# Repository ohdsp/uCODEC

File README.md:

# [Open Hardware DSP Platform](www.ohdsp.org)
## uCODEC 1.0 
### A 5cm x 5cm CODEC board using Analog Device AD1939
### 8 Differential Outputs
### 4 Differential Inputs
---
# README
### Disclaimer
Copyright Paul Janicki 2019

Licensed under the TAPR Open Hardware License (www.tapr.org/OHL)

This documentation is distributed WITHOUT ANY EXPRESS OR IMPLIED WARRANTY, INCLUDING OF MERCHANTABILITY, SATISFACTORY QUALITY AND FITNESS FOR A PARTICULAR PURPOSE.

### What is this repository for?

**Quick summary**

This is a simple 4 input, 8 output, ADC/DAC board using the Analog Devices AD1939 CODEC

This board forms part the of the open hardware DSP platform which is designed to be a highly customisable and flexible DSP platform. 

This repository contains the KiCad design files, manufacturing Gerber/drill files, and PDF/drawing files for this board.

### What is the project folder structure?
Most folder names are self explanatory. Starting from the top level:
*uCODEC*
+ *Bill of Materials*  - This contains the bill of materials in CVS, LibreOffice Calc and XML formats
+ *Drawings* - This contains PDF and SVG Schematic and PCB files
+ *Gerbers* - This contains the PCB Gerbers and drill drawings for manufacture, there is also a zip file ready to send to most manufacturers
+ *KiCad* - This contains the original KiCad schematic and PCB design files

### How do I get set up?

**Summary of set up**

1. Set your self up a directory on a local disk, something simple will make life easier (eg C:\Electronics on Windows as used here), but anywhere will do just fine.
2. Download the Kicad-Libs from [https://github.com/ohdsp/KiCad-Libs](https://github.com/ohdsp/KiCad-Libs) and place in C:\Electronics\Kicad-Libs (or your chosen folder) 
3. Create a OHDSP subdirectory in C:\Electronics (so C:\Electronics\OHDSP)
3. Download this project to C:\Electronics\OHDSP\uCODEC
4. Fire up Kicad
5. Open the main project file C:\Electronics\OHDSP\uCODEC\KiCad\uCODEC.pro
7. Do as you wish with the project, just keep it under the TAPR Open Hardware License.
Note: For library issues see below.

Make sure your git setup doesn't exclude files used in the project (like .LIB files) or things may go wrong down the line.

**KiCad Library Configuration**

Note that libraries are setup using relative paths, if you follow the above instructions things should work just fine. Below is the default library setup.

To setup eeschema component libraries:
From KiCad main window go to menu Tools -> Edit Schematic Symbols. In the new Window go to menu Preferences -> Manage Symbol Libraries.

On the new "Symbol Libraries" window select the "Project Specific Libraries" tab. The "Append Library" and "Remove Library" buttons can be used to add/remove enteries.
The standard setup is:

|   | Active | Nickname        | Library Path                                        | Plugin Type | Options | Description |
|---|--------|-----------------|-----------------------------------------------------|-------------|---------|-------------|
| 1 | Ticked | power           | ${KICAD_SYMBOL_DIR}/power.lib                       | Legacy      | (blank) | (blank)     |
| 2 | Ticked | MyKiCadLibs-Lib | ${KIPRJMOD}/../../../KiCad-Libs/MyKiCadLibs-Lib.lib | Legacy      | (blank) | (blank)     |

${KICAD_SYMBOL_DIR}  is set under the Enviromnet Variable Configuration. Close Symbol Libraries dialogue and go "Preferences" -> "Configure Paths..."

${KICAD_SYMBOL_DIR} is set to C:\Program Files\KiCad\share\kicad\library - this is the default for a KiCad install on the C drive

${KIPRJMOD} is automatically set to the location of the project (.pro file), in this example this would be C:\Electronics\OHDSP\uCODEC\KiCad

To setup Pcbnew libraries:
From KiCad main window go to menu Tools -> Edit PCB Footprints. In the new Window go to menu Preferences -> Manage Symbol Libraries.

On the new "Symbol Libraries" window select the "Project Specific Libraries" tab. The "Append Library" and "Remove Library" buttons can be used to add/remove enteries.
The standard setup is:

|   | Active | Nickname               | Library Path                                                  | Plugin Type | Options | Description |
|---|--------|------------------------|---------------------------------------------------------------|-------------|---------|-------------|
| 1 | Ticked | MyKiCadLibs-Footprints | ${KIPRJMOD}/../../../KiCad-Libs/MyKiCadLibs-Footprints.pretty | KiCad       | (blank) | (blank)     |

${KIPRJMOD} is automatically set to the location of the project (.pro file), in this example this would be C:\Electronics\OHDSP\uCODEC\KiCad

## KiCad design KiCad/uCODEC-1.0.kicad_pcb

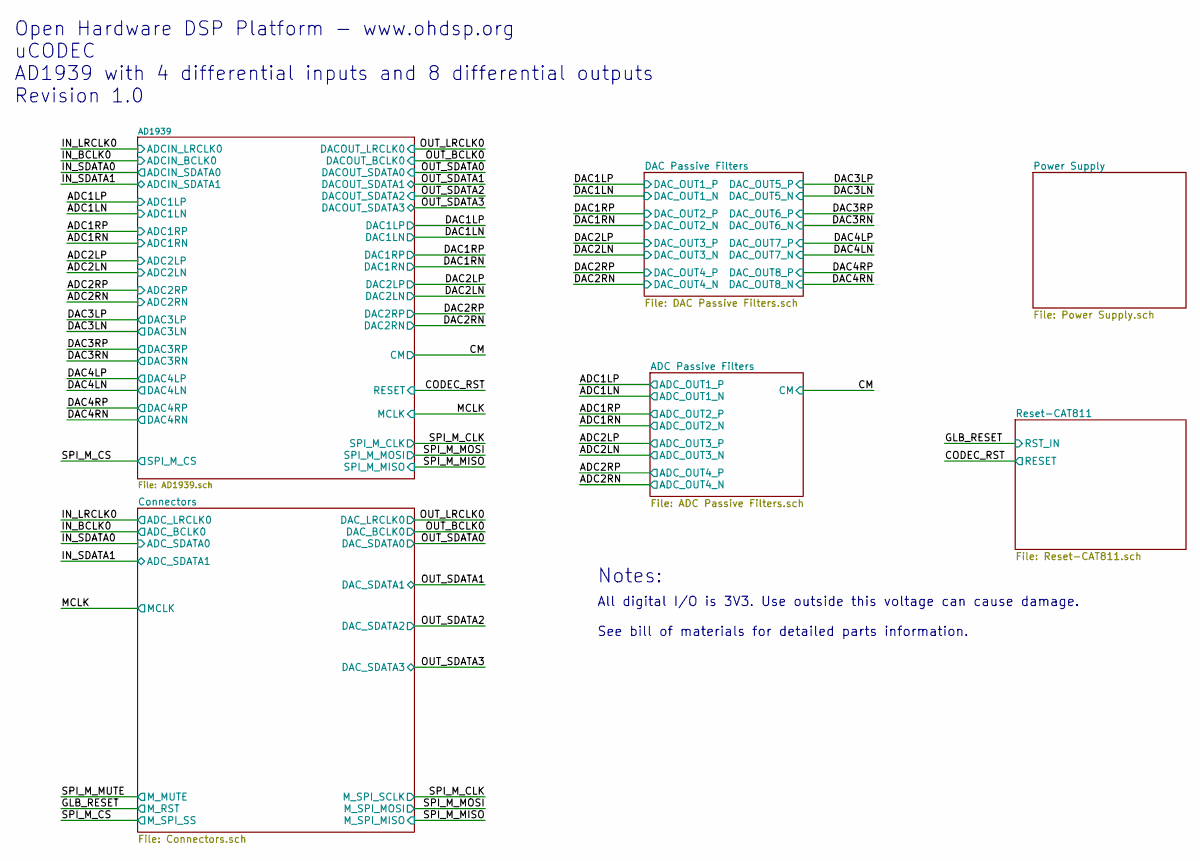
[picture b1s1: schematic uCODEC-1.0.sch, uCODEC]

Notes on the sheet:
All digital I/O is 3V3. Use outside this voltage can cause damage. See bill of materials for detailed parts information.
Notes:
Open Hardware DSP Platform - www.ohdsp.org uCODEC AD1939 with 4 differential inputs and 8 differential outputs Revision 1.0

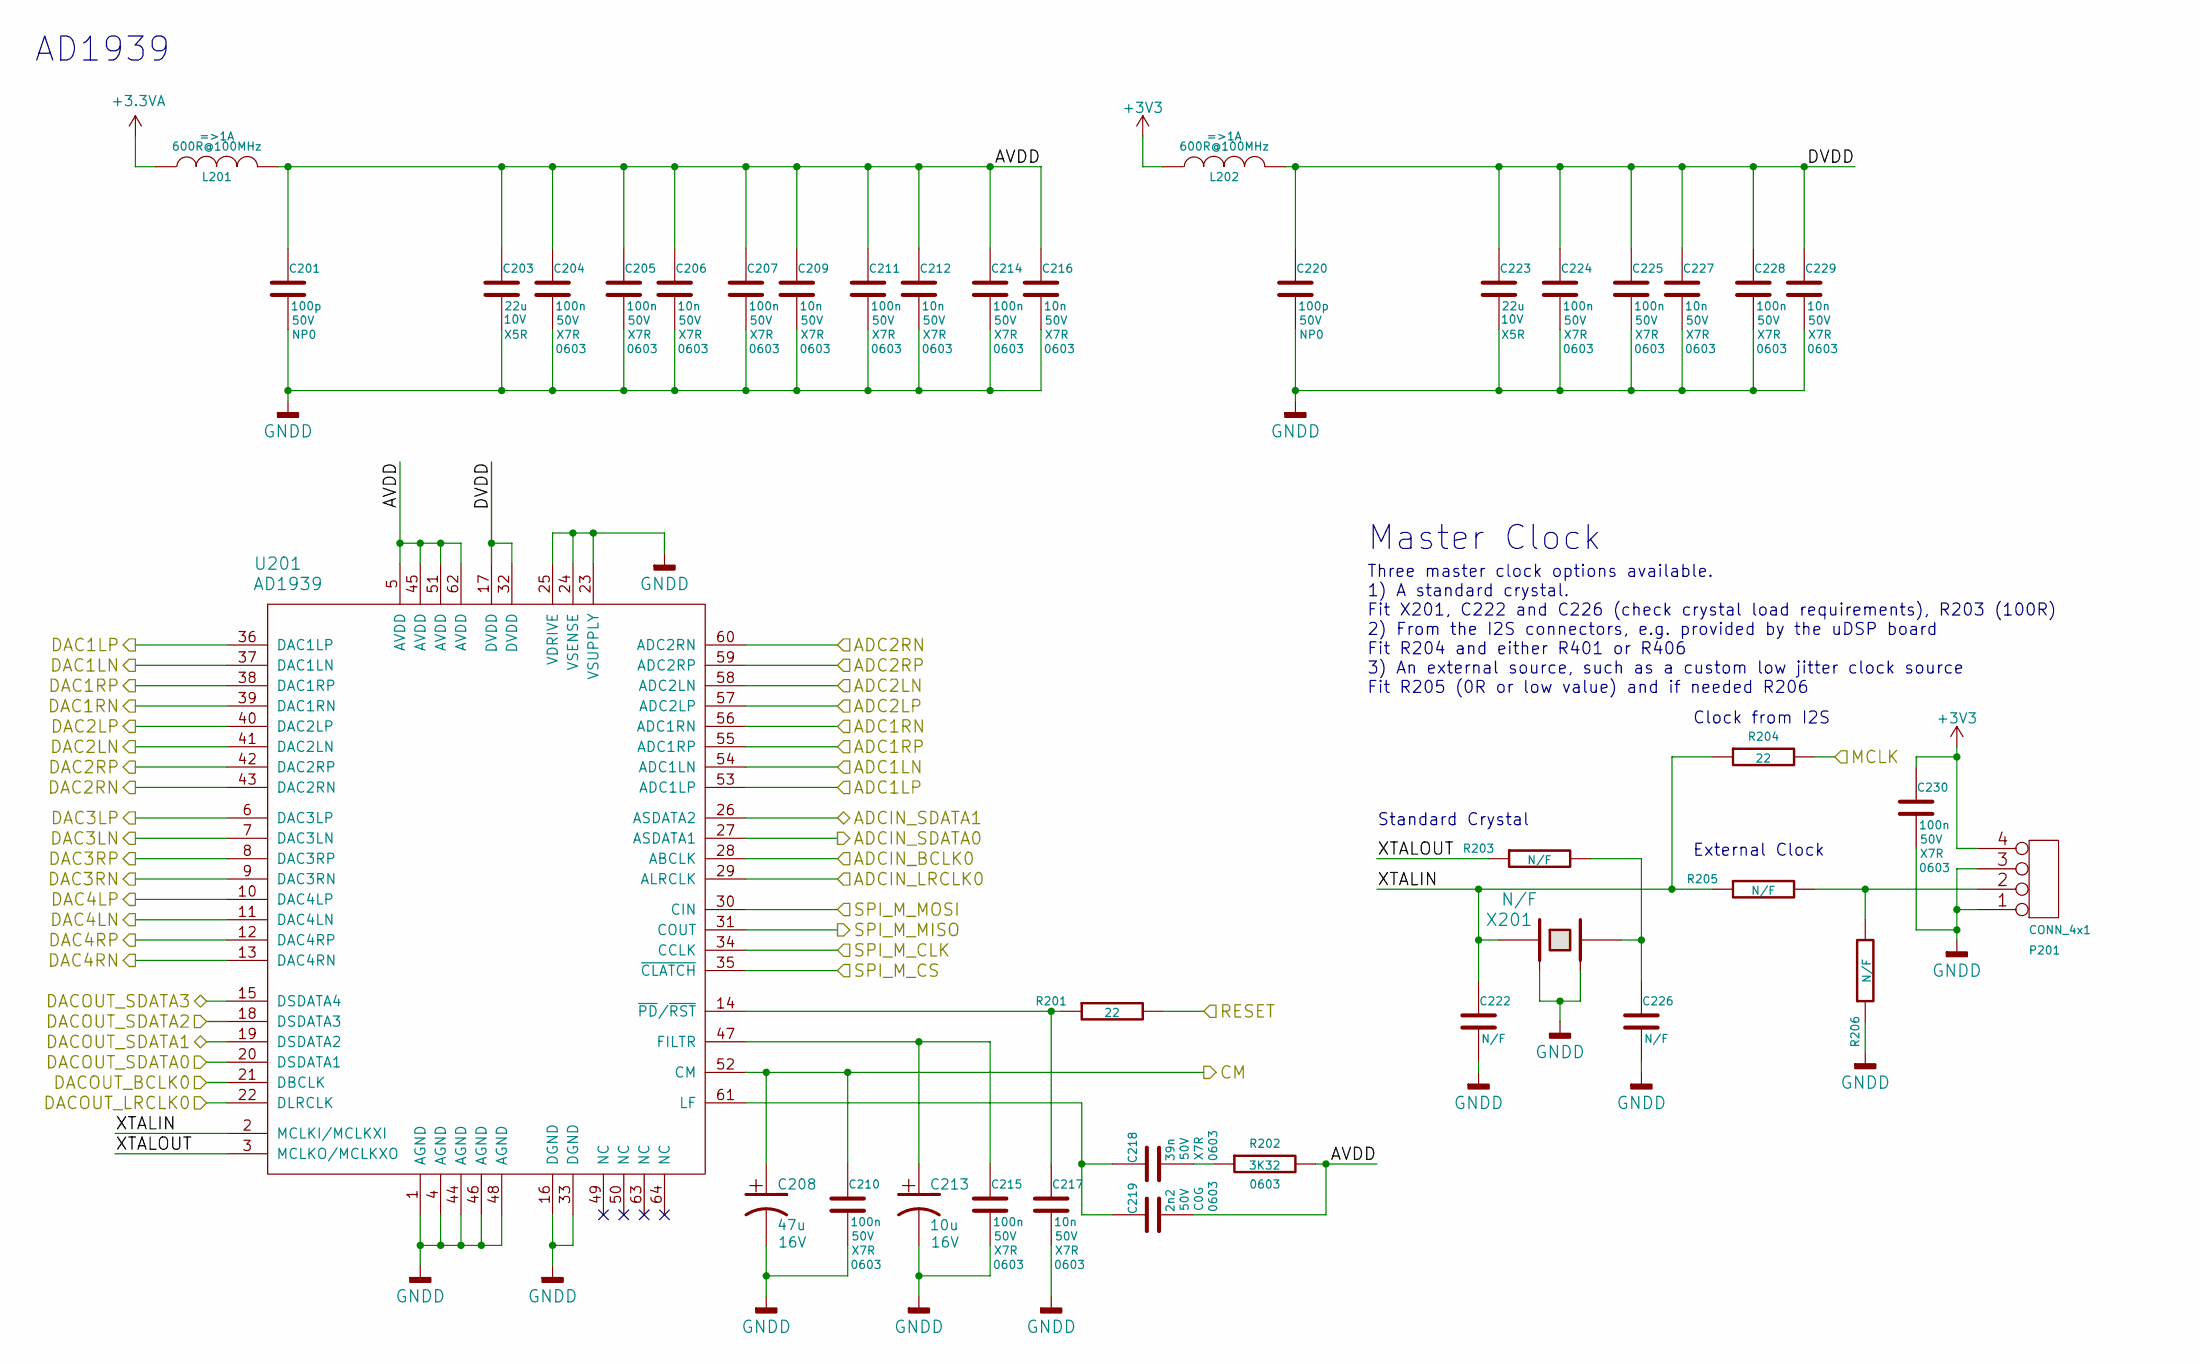
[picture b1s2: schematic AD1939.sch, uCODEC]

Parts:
C201, C220: 100p; SMD-0603; Voltage 50V; Tolerance 5%
C203, C223: 22u; SMD-0603; Voltage 10V; Tolerance 20%
C204, C205, C207, C210, C211, C214, C215, C224, C225, C228, C230: 100n; SMD-0603; Voltage 50V; Tolerance 10%
C206, C209, C212, C216, C217, C227, C229: 10n; SMD-0603; Voltage 50V; Tolerance 10%
C208: 47u; CAP-SMD-SIZE-D; Voltage 16V
C213: 10u; CAP-SMD-SIZE-B; Voltage 16V
C218: 39n; SMD-0603; Voltage 50V; Tolerance 10%
C219: 2n2; SMD-0603; Voltage 50V; Tolerance 5%
C222, C226: N/F; SMD-0603; Voltage 25V; Tolerance 5%
L201, L202: 600R@100MHz; SMD-0805
P201: CONN_4x1; CONN_SIL_4_1MM
R201, R204: 22; SMD-0603; Tolerance 1%
R202: 3K32; SMD-0603; Tolerance 1%
R203, R205, R206: N/F; SMD-0603; Tolerance 1%
U201: AD1939; IC-LQFP64
X201: N/F; XTAL_3.2x2.5_4PIN

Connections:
+3.3VA: L201.1; also elsewhere on the board
+3V3: C230.1, L202.1, P201.4; also elsewhere on the board
/AD1939/AVDD: C201.1, C203.1, C204.1, C205.1, C206.1, C207.1, C209.1, C211.1, C212.1, C214.1, C216.1, C219.2, L201.2, R202.2, U201.5 (AVDD), U201.45 (AVDD), U201.51 (AVDD), U201.62 (AVDD)
/AD1939/DVDD: C220.1, C223.1, C224.1, C225.1, C227.1, C228.1, C229.1, L202.2, U201.17 (DVDD), U201.32 (DVDD)
/AD1939/XTALIN: C222.1, R204.1, R205.1, U201.2 (MCLKI/MCLKXI), X201.1
/AD1939/XTALOUT: R203.1, U201.3 (MCLKO/MCLKXO)
/ADC1RN: U201.56 (ADC1RN); also elsewhere on the board
/ADC2LN: U201.58 (ADC2LN); also elsewhere on the board
/ADC2LP: U201.57 (ADC2LP); also elsewhere on the board
/ADC2RN: U201.60 (ADC2RN); also elsewhere on the board
/ADC2RP: U201.59 (ADC2RP); also elsewhere on the board
/CM: C208.1, C210.1, U201.52 (CM)
/CODEC_RST: R201.2; also elsewhere on the board
/DAC1LN: U201.37 (DAC1LN); also elsewhere on the board
/DAC1LP: U201.36 (DAC1LP); also elsewhere on the board
/DAC1RN: U201.39 (DAC1RN); also elsewhere on the board
/DAC1RP: U201.38 (DAC1RP); also elsewhere on the board
/DAC2LN: U201.41 (DAC2LN); also elsewhere on the board
/DAC2LP: U201.40 (DAC2LP); also elsewhere on the board
/DAC2RN: U201.43 (DAC2RN); also elsewhere on the board
/DAC2RP: U201.42 (DAC2RP); also elsewhere on the board
/DAC3LN: U201.7 (DAC3LN); also elsewhere on the board
/DAC3LP: U201.6 (DAC3LP); also elsewhere on the board
/DAC3RN: U201.9 (DAC3RN); also elsewhere on the board
/DAC3RP: U201.8 (DAC3RP); also elsewhere on the board
/DAC4LN: U201.11 (DAC4LN); also elsewhere on the board
/DAC4LP: U201.10 (DAC4LP); also elsewhere on the board
/DAC4RN: U201.13 (DAC4RN); also elsewhere on the board
/DAC4RP: U201.12 (DAC4RP); also elsewhere on the board
/IN_BCLK0: U201.28 (ABCLK); also elsewhere on the board
/IN_LRCLK0: U201.29 (ALRCLK); also elsewhere on the board
/IN_SDATA0: U201.27 (ASDATA1); also elsewhere on the board
/IN_SDATA1: U201.26 (ASDATA2); also elsewhere on the board
/MCLK: R204.2; also elsewhere on the board
/OUT_BCLK0: U201.21 (DBCLK); also elsewhere on the board
/OUT_LRCLK0: U201.22 (DLRCLK); also elsewhere on the board
/OUT_SDATA0: U201.20 (DSDATA1); also elsewhere on the board
/OUT_SDATA1: U201.19 (DSDATA2); also elsewhere on the board
/OUT_SDATA2: U201.18 (DSDATA3); also elsewhere on the board
/OUT_SDATA3: U201.15 (DSDATA4); also elsewhere on the board
/SPI_M_CLK: U201.34 (CCLK); also elsewhere on the board
/SPI_M_CS: U201.35 (~CLATCH); also elsewhere on the board
/SPI_M_MISO: U201.31 (COUT); also elsewhere on the board
/SPI_M_MOSI: U201.30 (CIN); also elsewhere on the board
unnamed: C213.1, C215.1, U201.47 (FILTR)
unnamed: C217.1, R201.1, U201.14 (~PD~/~RST)
unnamed: C218.1, C219.1, U201.61 (LF)
unnamed: C218.2, R202.1
unnamed: C226.1, R203.2, X201.3
unnamed: P201.2, R205.2, R206.2

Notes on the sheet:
Master Clock
Standard Crystal
External Clock
AD1939
Clock from I2S
Three master clock options available. 1) A standard crystal. Fit X201, C222 and C226 (check crystal load requirements), R203 (100R) 2) From the I2S connectors, e.g. provided by the uDSP board Fit R204 and either R401 or R406 3) An external source, such as a custom low jitter clock source Fit R205 (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

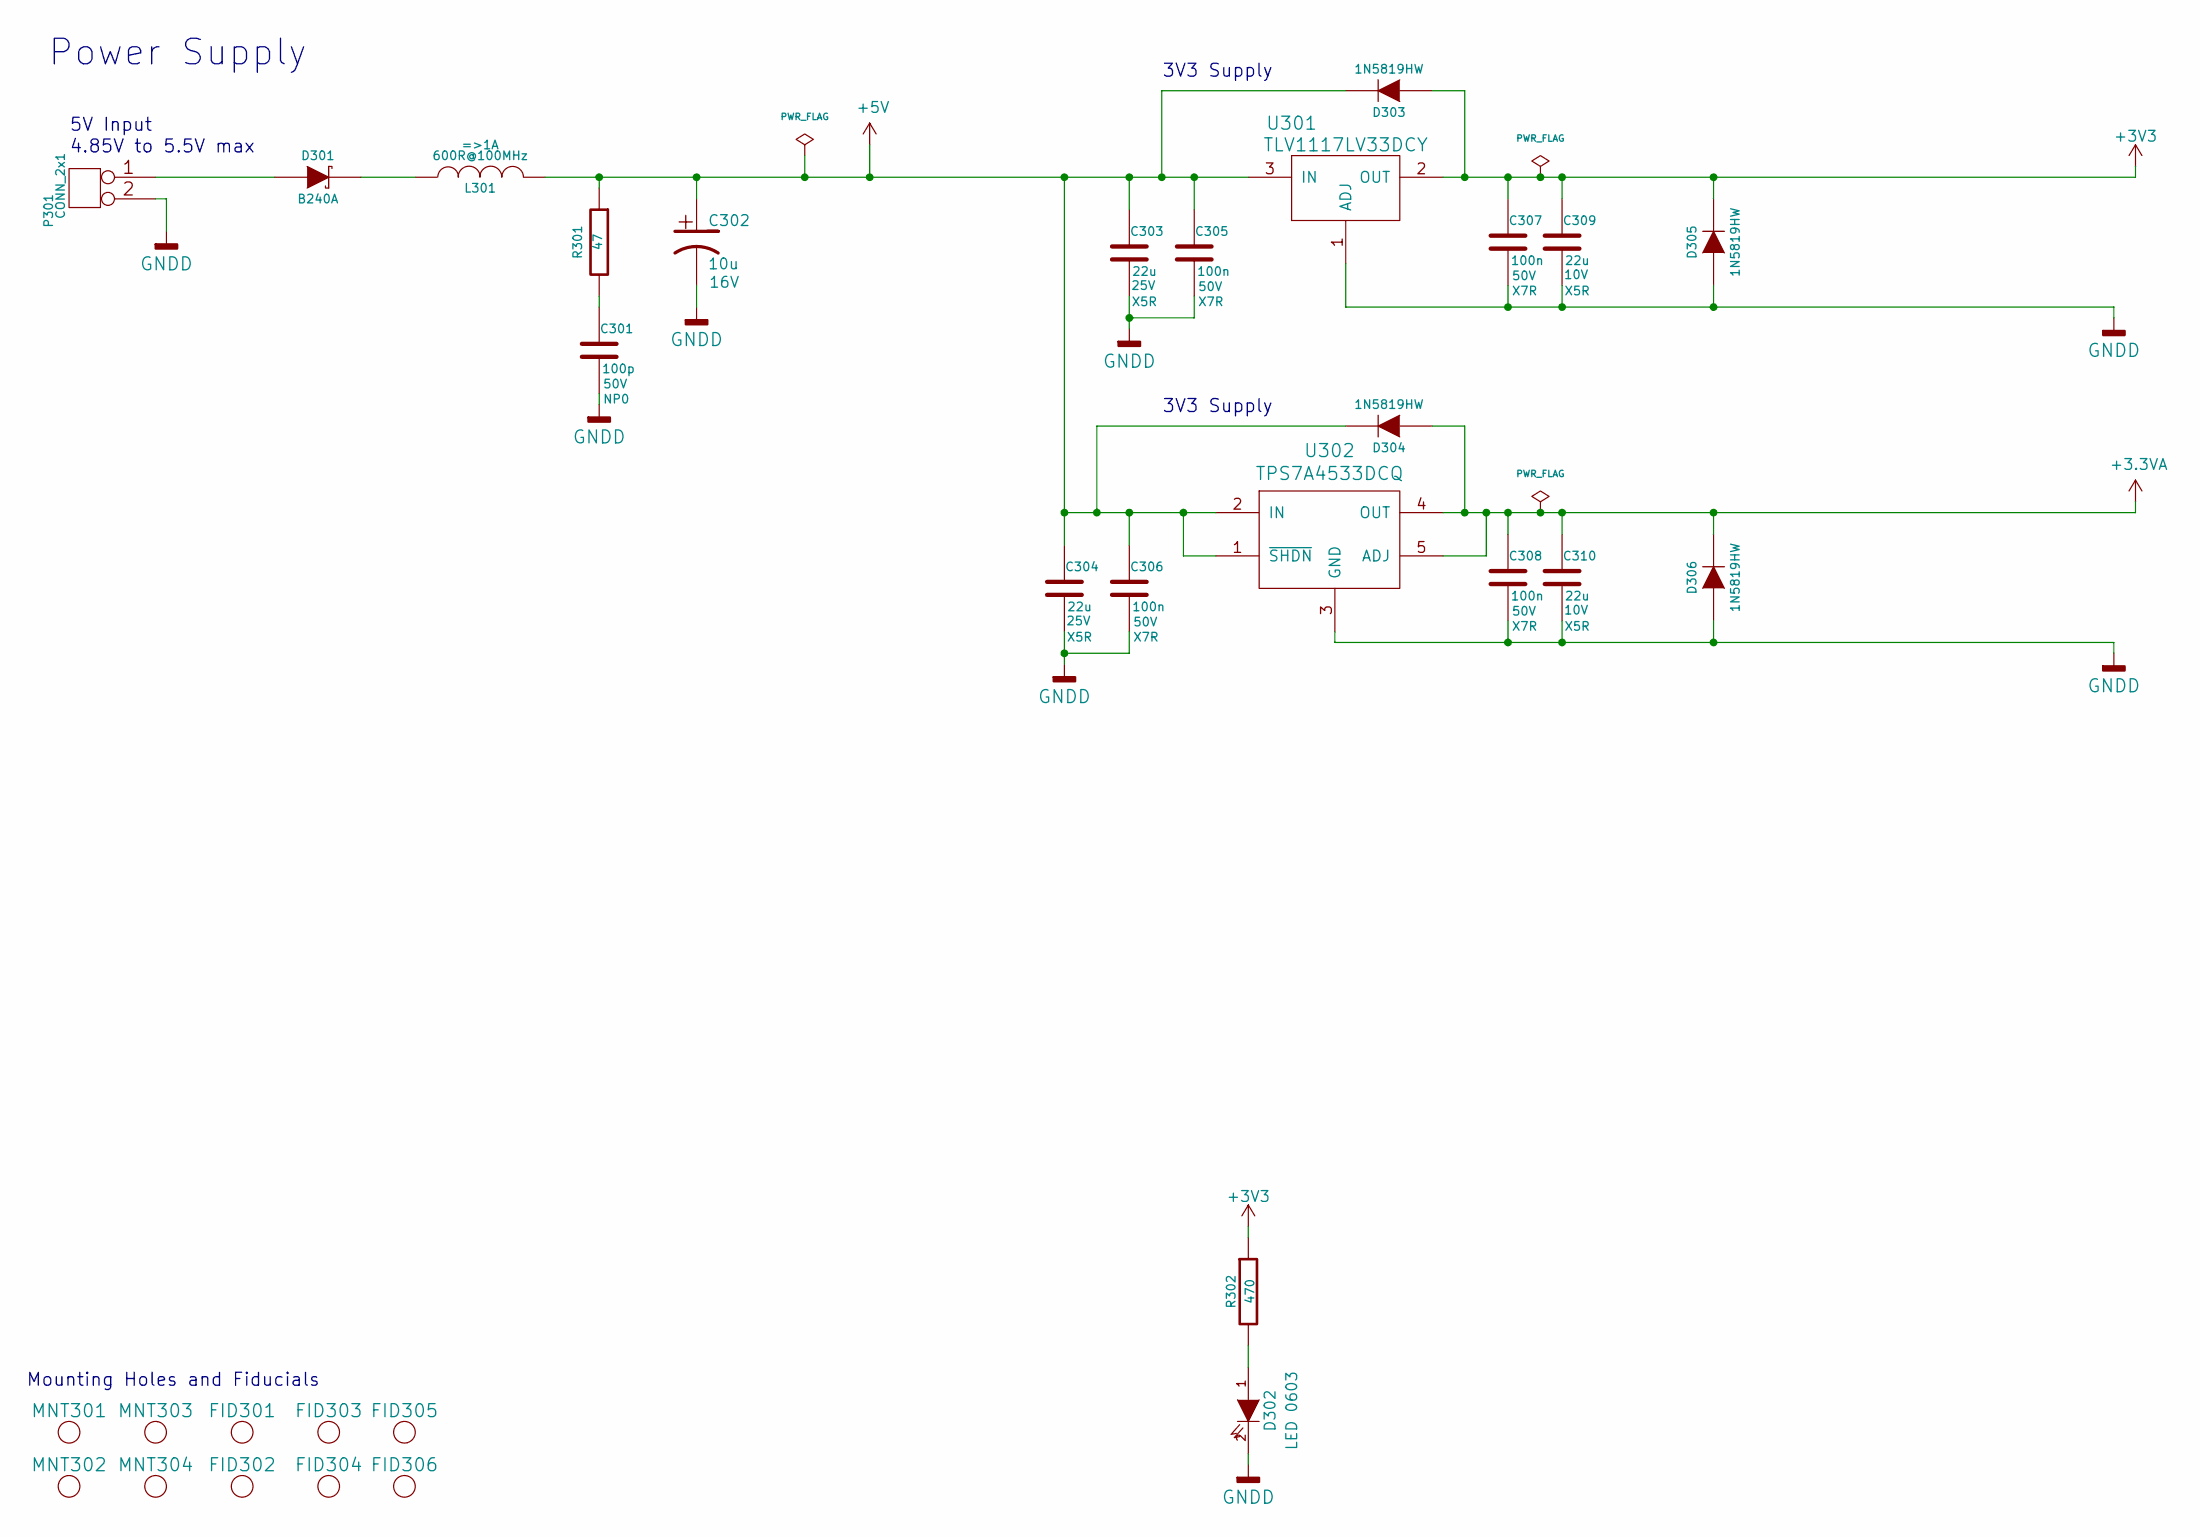
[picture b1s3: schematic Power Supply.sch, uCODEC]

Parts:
C301: 100p; SMD-0603; Voltage 50V; Tolerance 5%
C302: 10u; CAP-SMD-SIZE-B; Voltage 16V
C303, C304: 22u; SMD-0805; Voltage 25V; Tolerance 20%
C305, C306, C307, C308: 100n; SMD-0603; Voltage 50V; Tolerance 10%
C309, C310: 22u; SMD-0603; Voltage 10V; Tolerance 20%
D301: B240A; DIODE-SMA
D302: LED 0603; SMD-0603-LED
D303, D304, D305, D306: 1N5819HW; DIODE-SOD-123
FID301, FID302, FID303, FID304, FID305, FID306: MNT_HOLE; FID-1MM-2MM
L301: 600R@100MHz; SMD-0805
MNT301, MNT302, MNT303, MNT304: MNT_HOLE; MNT_HOLE_3.2mm
P301: CONN_2x1; CONN-2WAY-2.54mm-3.81mm-SPACING
R301: 47; SMD-0603; Tolerance 1%
R302: 470; SMD-0603; Tolerance 1%
U301: TLV1117LV33DCY; IC-SOT-223
U302: TPS7A4533DCQ; IC-SOT223-6

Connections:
+3.3VA: C308.1, C310.1, D304.1 (A), D306.2 (K), U302.4 (OUT), U302.5 (ADJ); also elsewhere on the board
+3V3: C307.1, C309.1, D303.1 (A), D305.2 (K), R302.1, U301.2 (OUT); also elsewhere on the board
+5V: C302.1, C303.1, C304.1, C305.1, C306.1, D303.2 (K), D304.2 (K), L301.2, R301.1, U301.3 (IN), U302.1 (~SHDN), U302.2 (IN)
unnamed: C301.1, R301.2
unnamed: D301.1 (A), P301.1
unnamed: D301.2 (K), L301.1
unnamed: D302.1 (A), R302.2

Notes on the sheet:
Power Supply
5V Input
3V3 Supply
Mounting Holes and Fiducials
4.85V to 5.5V max

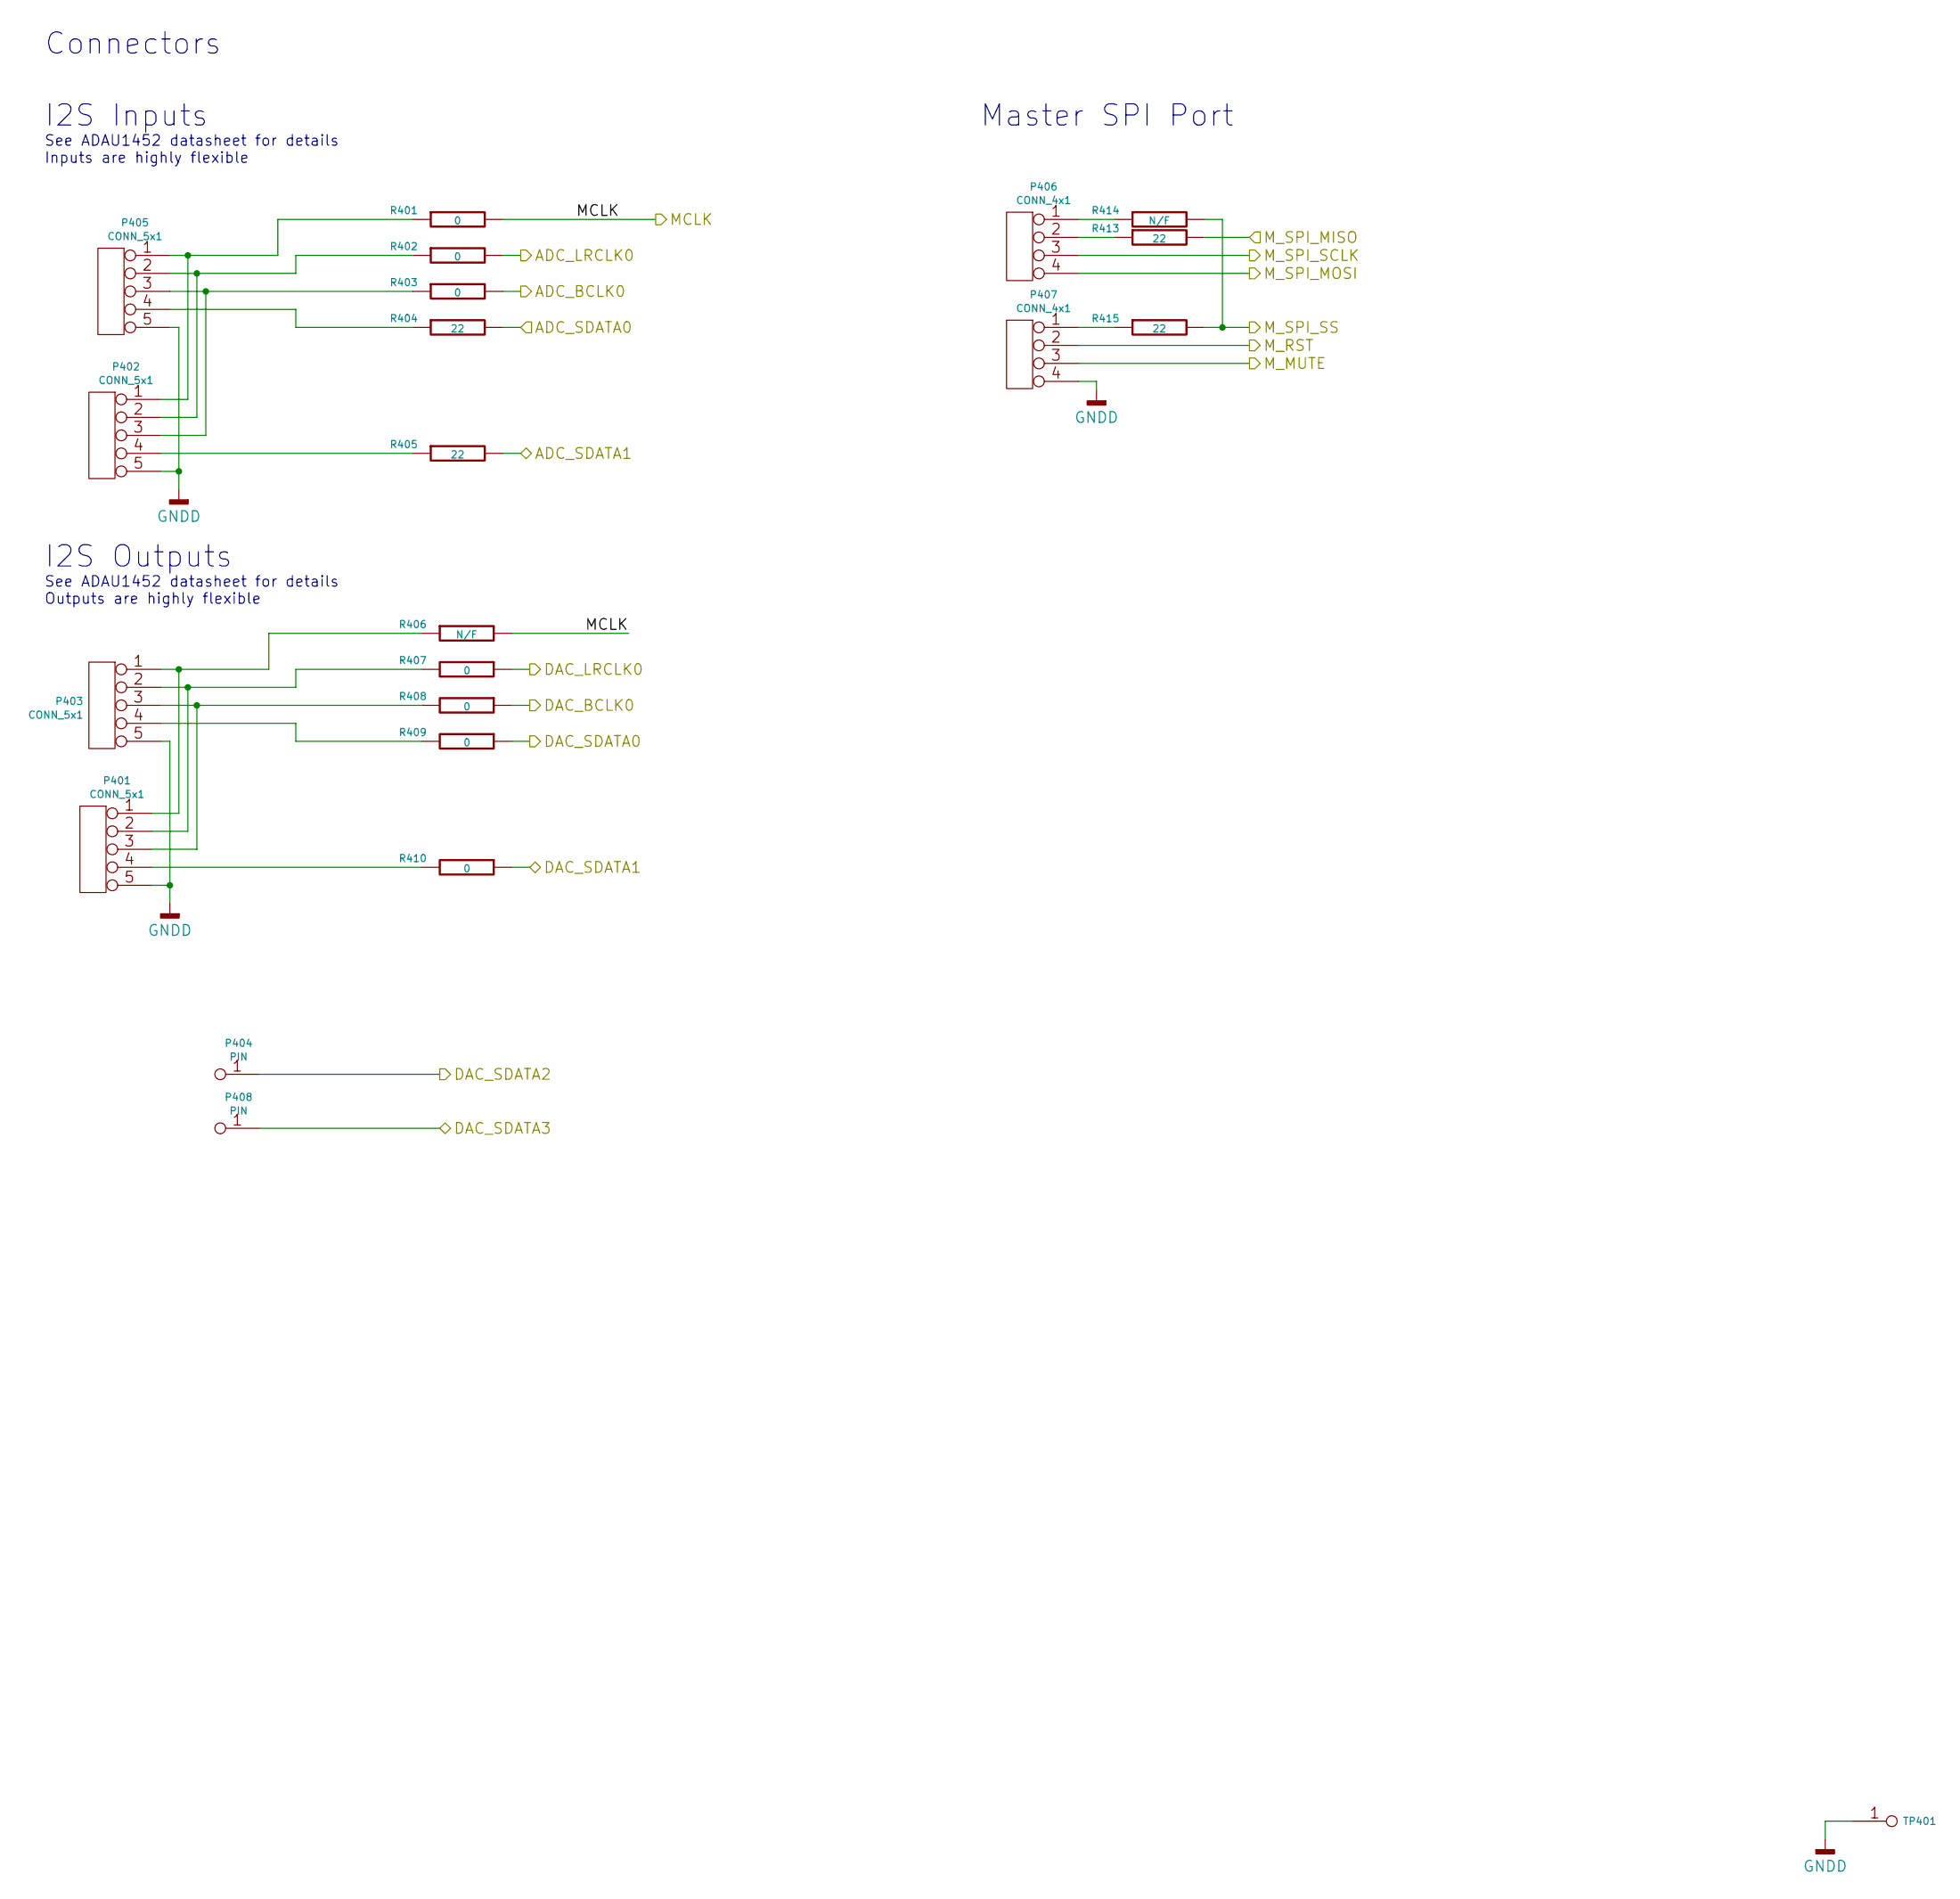
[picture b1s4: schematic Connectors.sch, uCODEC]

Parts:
P401, P402, P403, P405: CONN_5x1; CONN_SIL_5_1MM
P404, P408: PIN; TP-1mm
P406, P407: CONN_4x1; CONN_SIL_4_1MM
R401, R402, R403, R407, R408, R409, R410: 0; SMD-0603; Tolerance 1%
R404, R405, R413, R415: 22; SMD-0603; Tolerance 1%
R406, R414: N/F; SMD-0603; Tolerance 1%
TP401: PIN; TP-TH-1mm

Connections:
/GLB_RESET: P407.2; also elsewhere on the board
/IN_BCLK0: R403.2; also elsewhere on the board
/IN_LRCLK0: R402.2; also elsewhere on the board
/IN_SDATA0: R404.2; also elsewhere on the board
/IN_SDATA1: R405.2; also elsewhere on the board
/MCLK: R401.2, R406.2; also elsewhere on the board
/OUT_BCLK0: R408.1; also elsewhere on the board
/OUT_LRCLK0: R407.1; also elsewhere on the board
/OUT_SDATA0: R409.1; also elsewhere on the board
/OUT_SDATA1: R410.1; also elsewhere on the board
/OUT_SDATA2: P404.1; also elsewhere on the board
/OUT_SDATA3: P408.1; also elsewhere on the board
/SPI_M_CLK: P406.3; also elsewhere on the board
/SPI_M_CS: R414.2, R415.2; also elsewhere on the board
/SPI_M_MISO: R413.2; also elsewhere on the board
/SPI_M_MOSI: P406.4; also elsewhere on the board
unnamed: P401.1, P403.1, R406.1
unnamed: P401.2, P403.2, R407.2
unnamed: P401.3, P403.3, R408.2
unnamed: P401.4, R410.2
unnamed: P402.1, P405.1, R401.1
unnamed: P402.2, P405.2, R402.1
unnamed: P402.3, P405.3, R403.1
unnamed: P402.4, R405.1
unnamed: P403.4, R409.2
unnamed: P405.4, R404.1
unnamed: P406.1, R414.1
unnamed: P406.2, R413.1
unnamed: P407.1, R415.1

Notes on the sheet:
I2S Inputs
See ADAU1452 datasheet for details Inputs are highly flexible
I2S Outputs
See ADAU1452 datasheet for details Outputs are highly flexible
Master SPI Port
Connectors

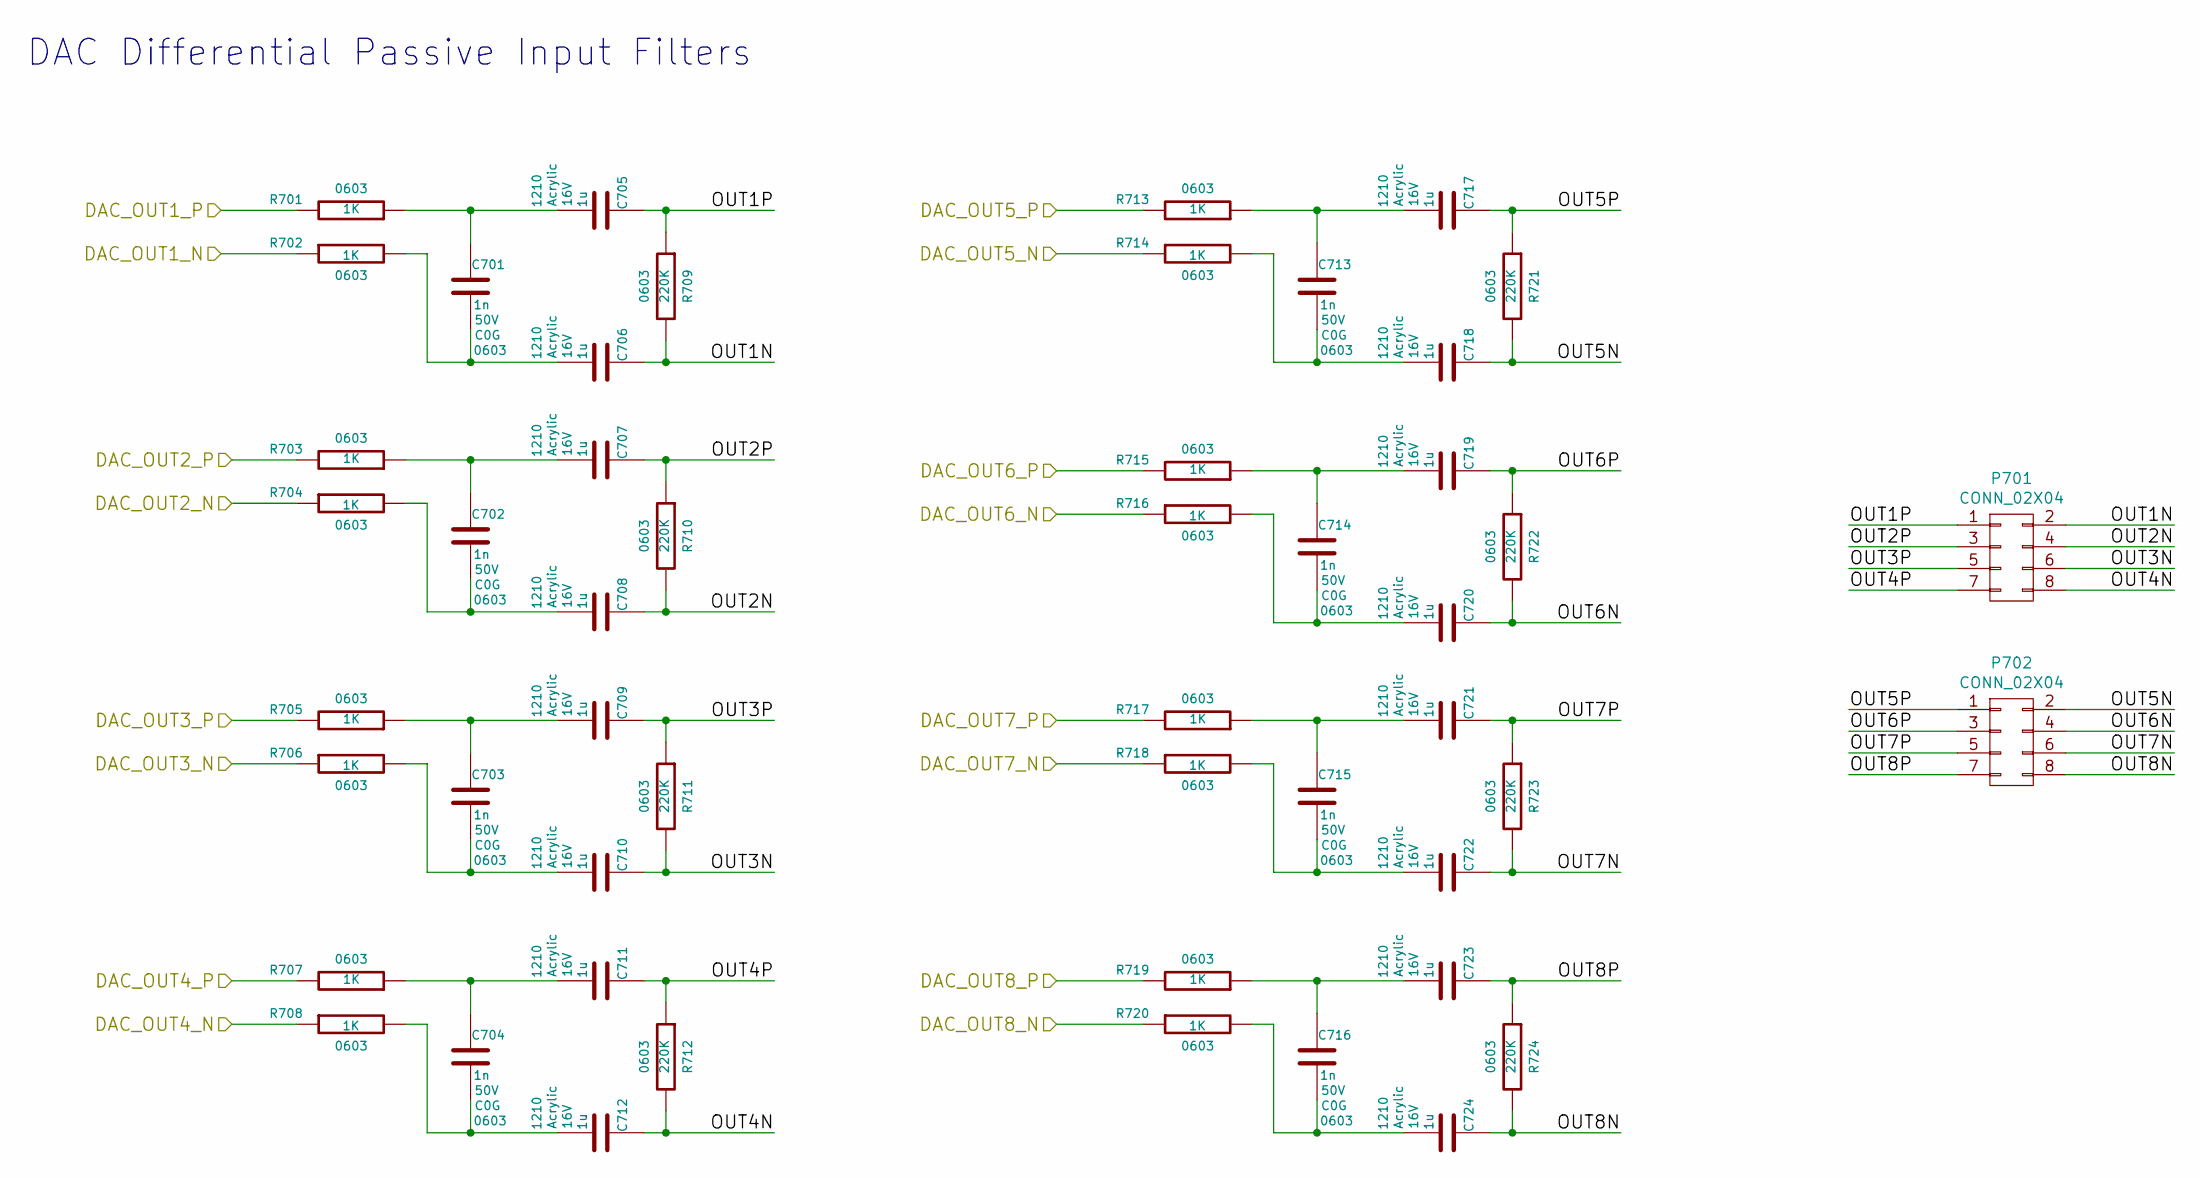
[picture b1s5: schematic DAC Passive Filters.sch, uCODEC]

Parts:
C701, C702, C703, C704, C713, C714, C715, C716: 1n; SMD-0603; Voltage 50V; Tolerance 5%
C705, C706, C707, C708, C709, C710, C711, C712, C717, C718, C719, C720, C721, C722, C723, C724: 1u; SMD-1210; Voltage 16V; Tolerance 20%
P701, P702: CONN_02X04; CONN_DIL_2X04
R701, R702, R703, R704, R705, R706, R707, R708, R713, R714, R715, R716, R717, R718, R719, R720: 1K; SMD-0603; Tolerance 1%
R709, R710, R711, R712, R721, R722, R723, R724: 220K; SMD-0603; Tolerance 1%

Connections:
/DAC1LN: R702.1; also elsewhere on the board
/DAC1LP: R701.2; also elsewhere on the board
/DAC1RN: R704.1; also elsewhere on the board
/DAC1RP: R703.2; also elsewhere on the board
/DAC2LN: R706.1; also elsewhere on the board
/DAC2LP: R705.2; also elsewhere on the board
/DAC2RN: R708.1; also elsewhere on the board
/DAC2RP: R707.2; also elsewhere on the board
/DAC3LN: R714.1; also elsewhere on the board
/DAC3LP: R713.2; also elsewhere on the board
/DAC3RN: R716.1; also elsewhere on the board
/DAC3RP: R715.2; also elsewhere on the board
/DAC4LN: R718.1; also elsewhere on the board
/DAC4LP: R717.2; also elsewhere on the board
/DAC4RN: R720.1; also elsewhere on the board
/DAC4RP: R719.2; also elsewhere on the board
/DAC Passive Filters/OUT1N: C706.1, P701.2, R709.2
/DAC Passive Filters/OUT1P: C705.1, P701.1, R709.1
/DAC Passive Filters/OUT2N: C708.1, P701.4, R710.2
/DAC Passive Filters/OUT2P: C707.1, P701.3, R710.1
/DAC Passive Filters/OUT3N: C710.1, P701.6, R711.2
/DAC Passive Filters/OUT3P: C709.1, P701.5, R711.1
/DAC Passive Filters/OUT4N: C712.1, P701.8, R712.2
/DAC Passive Filters/OUT4P: C711.1, P701.7, R712.1
/DAC Passive Filters/OUT5N: C718.1, P702.2, R721.2
/DAC Passive Filters/OUT5P: C717.1, P702.1, R721.1
/DAC Passive Filters/OUT6N: C720.1, P702.4, R722.2
/DAC Passive Filters/OUT6P: C719.1, P702.3, R722.1
/DAC Passive Filters/OUT7N: C722.1, P702.6, R723.2
/DAC Passive Filters/OUT7P: C721.1, P702.5, R723.1
/DAC Passive Filters/OUT8N: C724.1, P702.8, R724.2
/DAC Passive Filters/OUT8P: C723.1, P702.7, R724.1
unnamed: C701.1, C705.2, R701.1
unnamed: C701.2, C706.2, R702.2
unnamed: C702.1, C707.2, R703.1
unnamed: C702.2, C708.2, R704.2
unnamed: C703.1, C709.2, R705.1
unnamed: C703.2, C710.2, R706.2
unnamed: C704.1, C711.2, R707.1
unnamed: C704.2, C712.2, R708.2
unnamed: C713.1, C717.2, R713.1
unnamed: C713.2, C718.2, R714.2
unnamed: C714.1, C719.2, R715.1
unnamed: C714.2, C720.2, R716.2
unnamed: C715.1, C721.2, R717.1
unnamed: C715.2, C722.2, R718.2
unnamed: C716.1, C723.2, R719.1
unnamed: C716.2, C724.2, R720.2

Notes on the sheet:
DAC Differential Passive Input Filters

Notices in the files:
KiCad/uCODEC-1.0.kicad_pcb:
Copyright ©
